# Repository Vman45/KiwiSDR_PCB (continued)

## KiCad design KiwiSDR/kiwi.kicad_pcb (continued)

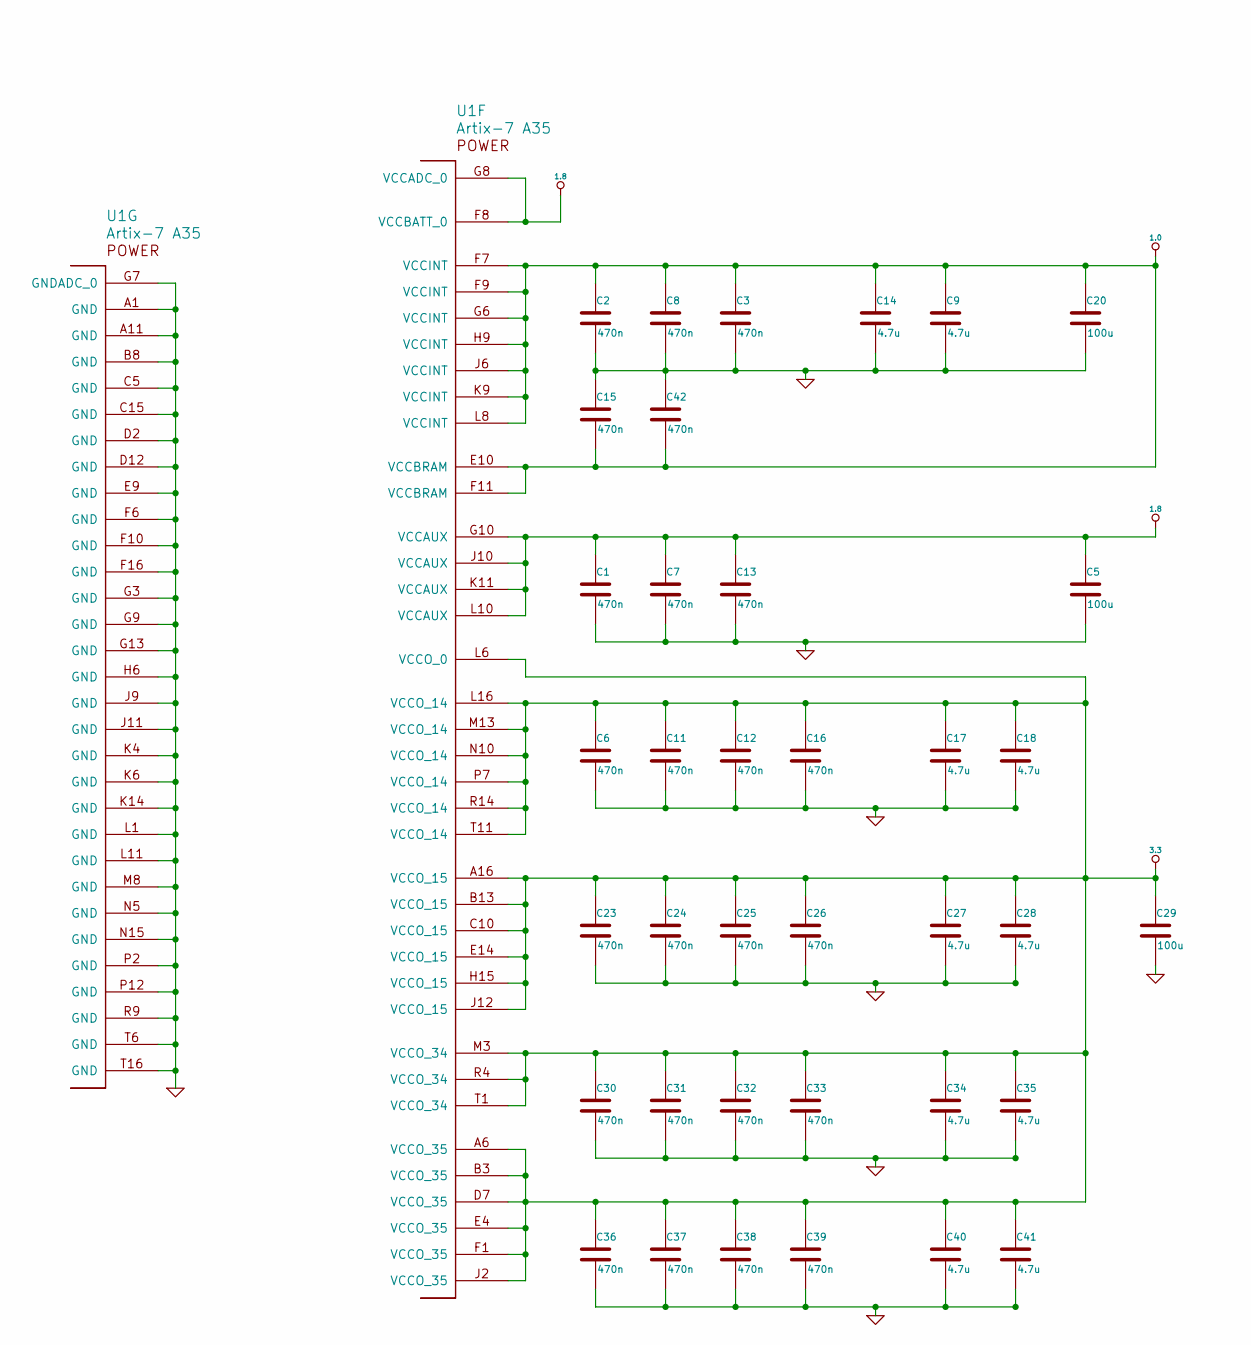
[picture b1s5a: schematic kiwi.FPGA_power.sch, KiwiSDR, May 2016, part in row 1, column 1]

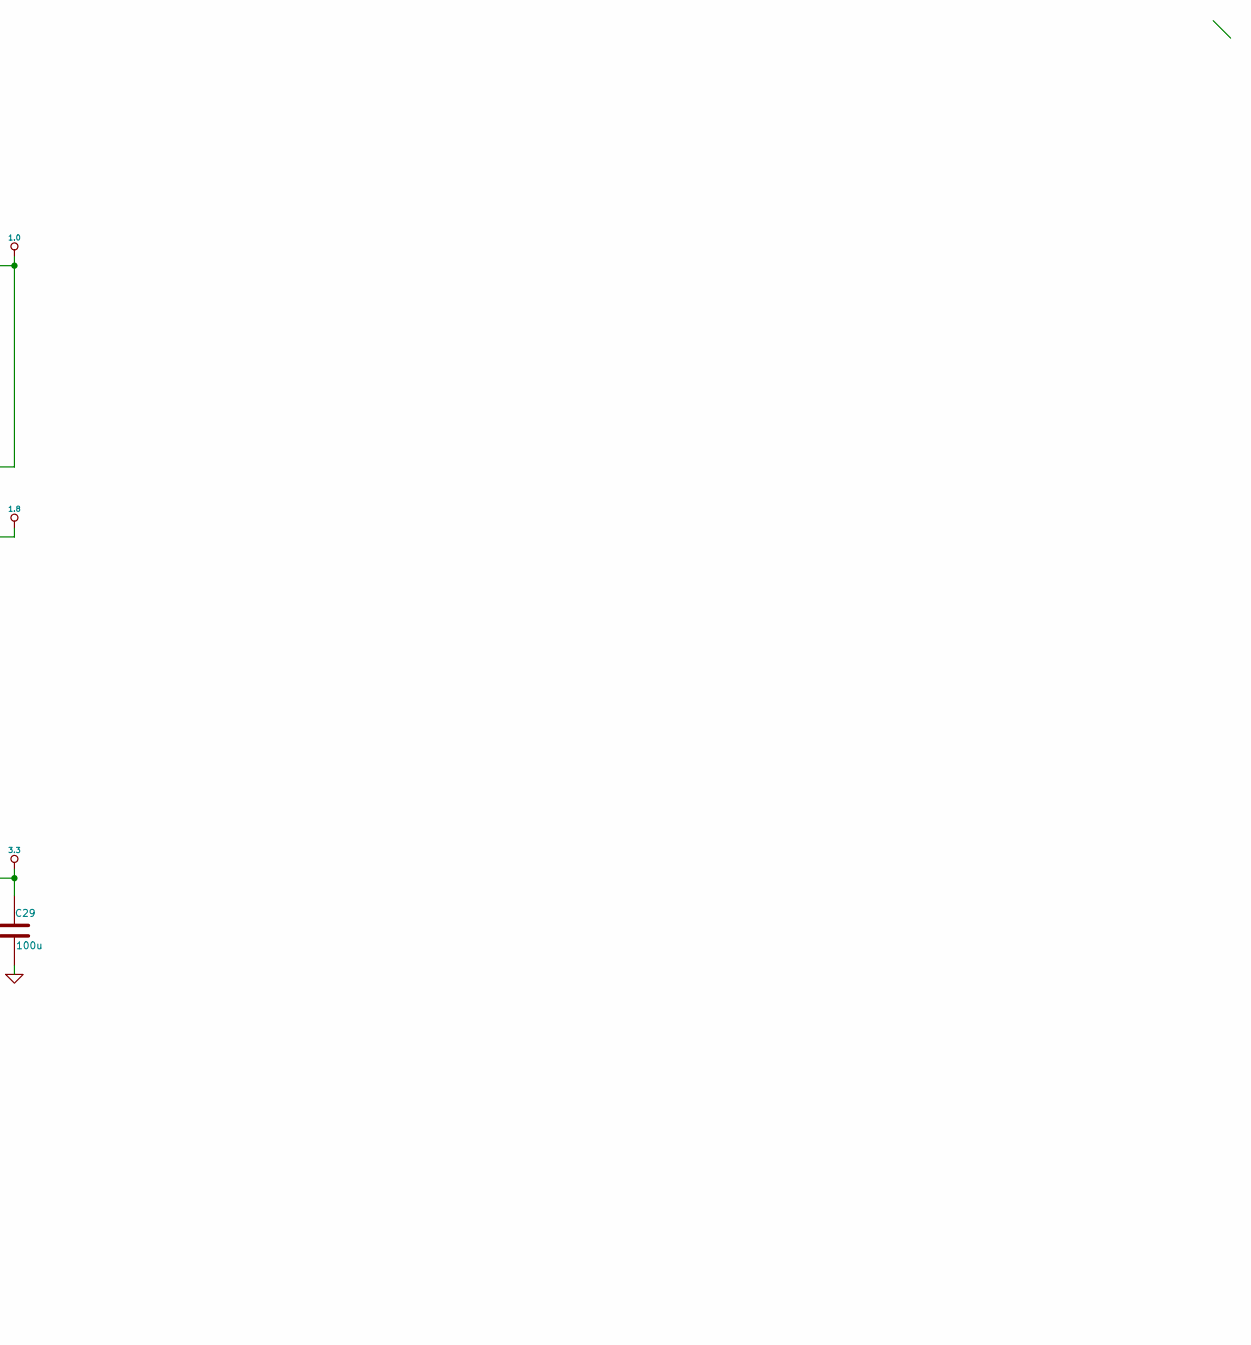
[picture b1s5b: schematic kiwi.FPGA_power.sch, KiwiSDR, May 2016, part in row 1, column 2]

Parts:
C1, C2, C3, C6, C7, C8, C11, C12, C13, C15, C16, C23, C24, C25, C26, C30, C31, C32, C33, C36, C37, C38, C39, C42: 470n; kiwi-SM0402
C5, C20, C29: 100u; kiwi-SM1206
C9, C14, C17, C18, C27, C28, C34, C35, C40, C41: 4.7u; kiwi-SM0402
U1: Artix-7 A35; kiwi-FTG256

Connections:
1.0: C2.1, C3.1, C8.1, C9.1, C14.1, C15.2, C20.1, C42.2, U1.E10 (VCCBRAM), U1.F7 (VCCINT), U1.F9 (VCCINT), U1.F11 (VCCBRAM), U1.G6 (VCCINT), U1.H9 (VCCINT), U1.J6 (VCCINT), U1.K9 (VCCINT), U1.L8 (VCCINT); also elsewhere on the board
1.8: C1.1, C5.1, C7.1, C13.1, U1.F8 (VCCBATT_0), U1.G8 (VCCADC_0), U1.G10 (VCCAUX), U1.J10 (VCCAUX), U1.K11 (VCCAUX), U1.L10 (VCCAUX); also elsewhere on the board

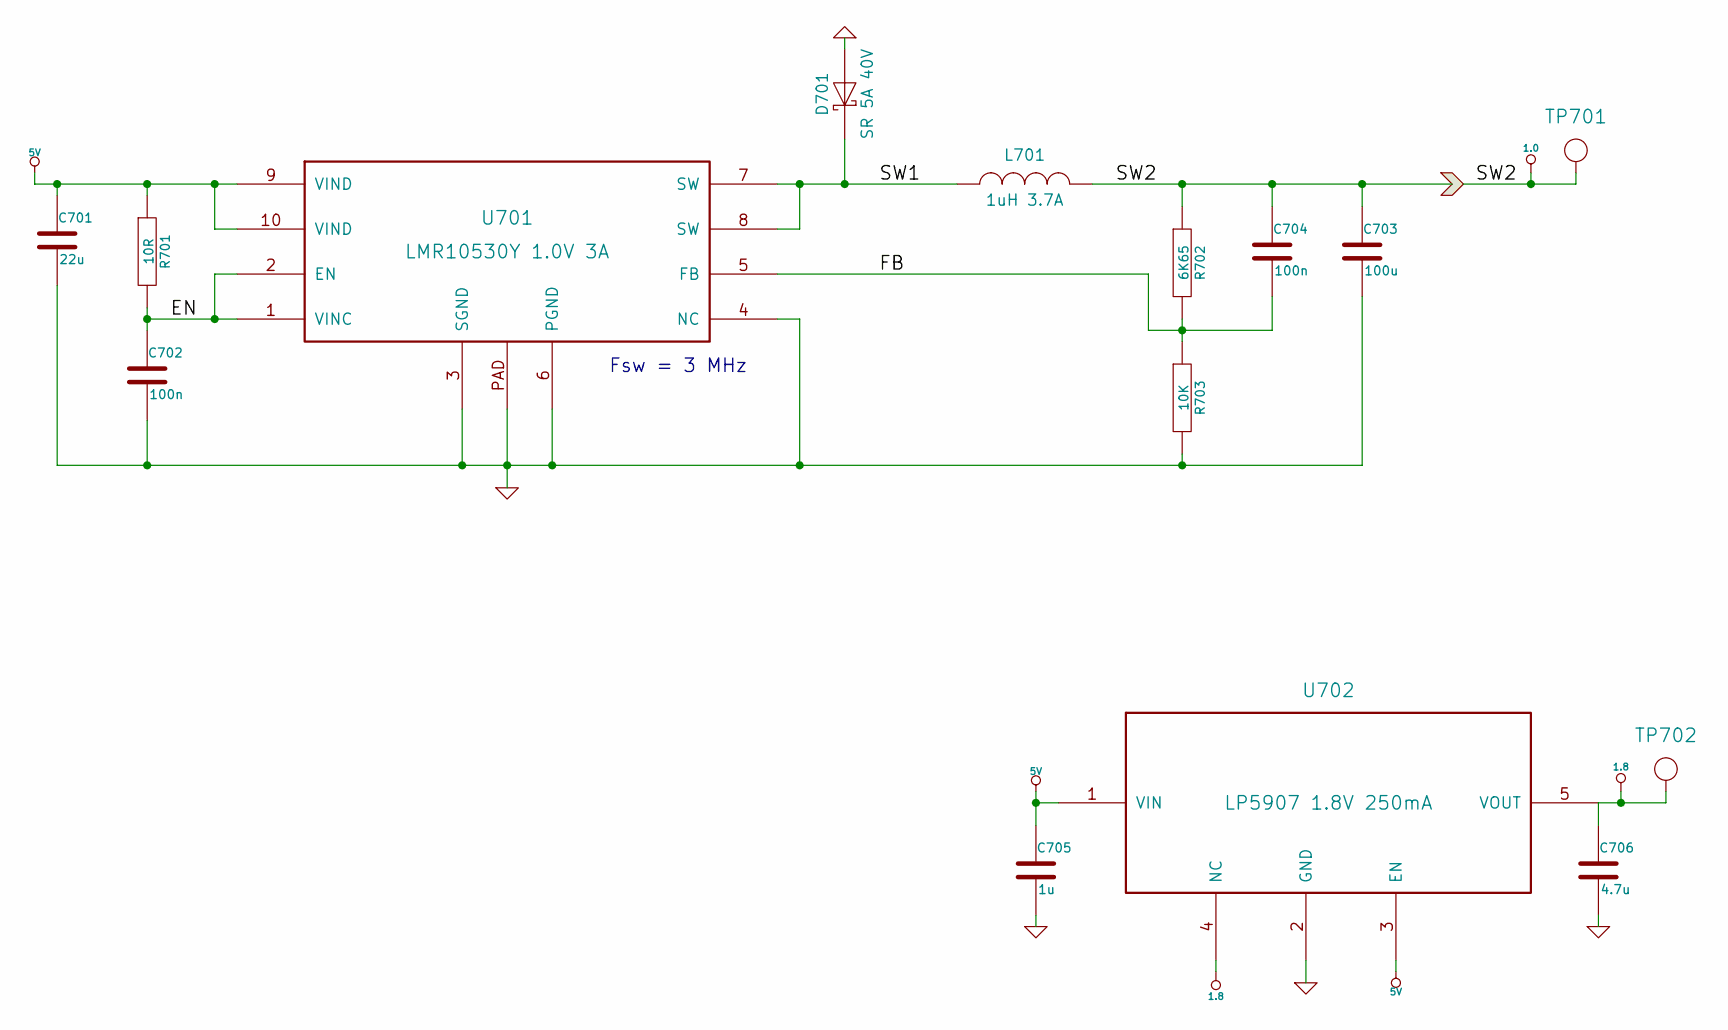
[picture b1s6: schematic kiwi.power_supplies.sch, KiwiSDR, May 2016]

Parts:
C701: 22u; kiwi-SM0805
C702, C704: 100n; kiwi-SM0402
C703: 100u; kiwi-SM1206
C705: 1u; kiwi-SM0402
C706: 4.7u; kiwi-SM0402
D701: SR 5A 40V; kiwi-DO214_AA
L701: 1uH 3.7A; kiwi-INDUCTOR_4x4
R701: 10R; kiwi-SM0402
R702: 6K65; kiwi-SM0402
R703: 10K; kiwi-SM0402
TP701, TP702: TEST_POINT; kiwi-TP_600
U701: LMR10530Y 1.0V 3A; kiwi-WSON10
U702: LP5907 1.8V 250mA; kiwi-SOT23_5

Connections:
1.0: C703.1, C704.1, L701.2, R702.1, TP701.1; also elsewhere on the board
1.8: C706.1, TP702.1, U702.4 (NC), U702.5 (VOUT); also elsewhere on the board
/Power_Supplies/EN: C702.1, R701.2, U701.1 (VINC), U701.2 (EN)
/Power_Supplies/FB: C704.2, R702.2, R703.1, U701.5 (FB)
/Power_Supplies/SW1: D701.1 (K), L701.1, U701.7 (SW), U701.8 (SW)

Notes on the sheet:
Fsw = 3 MHz

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
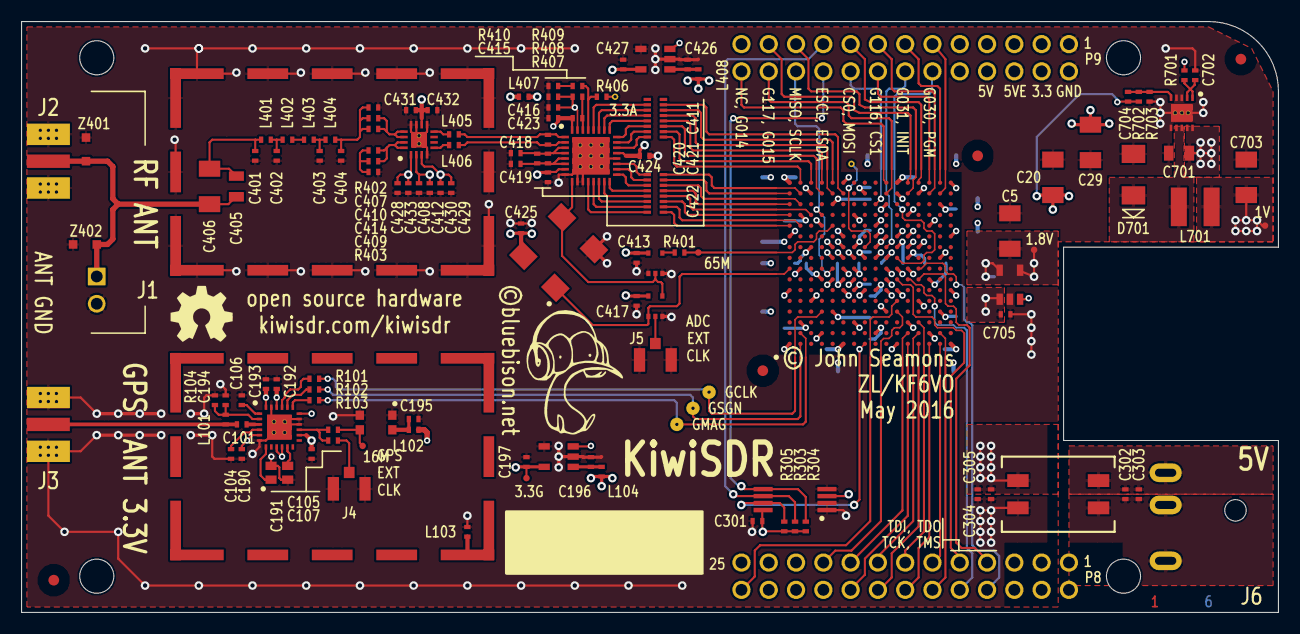
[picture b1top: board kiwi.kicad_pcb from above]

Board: 6 copper layers, 117.0 x 55.0 mm, 174 parts (0 on the bottom side), 119 nets.

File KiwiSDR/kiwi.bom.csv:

#1, 1, 0R, Panasonic, ERJ-2GE0R00X, kiwi-SM0402, R408
#2, 1, 10R, Panasonic, ERJ-2RKF10R0X, kiwi-SM0402, R701
#3, 1, 28R7, Panasonic, ERJ-2RKF28R7X, kiwi-SM0402, R403
#4, 1, 66R5, Panasonic, ERJ-2RKF66R5X, kiwi-SM0402, R402
#5, 4, 100R, Panasonic, ERJ-2RKF1000X, kiwi-SM0402, R101 R102 R103 R401
#6, 1, 1K5, Panasonic, ERJ-2RKF1501X, kiwi-SM0402, R104
#7, 3, 5K6, Panasonic, ERJ-2RKF5601X, kiwi-SM0402, R303 R304 R305
#8, 1, 6K65, Panasonic, ERJ-2RKF6651X, kiwi-SM0402, R702
#9, 4, 10K, Panasonic, ERJ-2RKF1002X, kiwi-SM0402, R406 R409 R410 R703
#10, 2, 100R, Bourns, CAY16-101J8LF, kiwi-RNET_CAY16_J8, R404 R405
#11, 2, 22p, Murata, GRM1555C1H220JA01D, kiwi-SM0402, C101 C104
#12, 2, 56p/100, Murata, GRM1555C2A560JA01D, kiwi-SM0402, C401 C404
#13, 4, 100p, Murata, GRM1555C1H101JA01D, kiwi-SM0402, C194 C408 C411 C416
#14, 2, 160p/50, Murata, GRM1555C1H161JA01D, kiwi-SM0402, C402 C403
#15, 5, 1n, Murata, GCM155R71H102KA37D, kiwi-SM0402, C407 C409 C428 C430 C432
#16, 8, 10n, Murata, GRM155R71C103KA01D, kiwi-SM0402, C105 C106 C193 C303 C305 C413 C417 C425
#17, 14, 100n, Murata, GRM155R71C104KA88D, kiwi-SM0402, C190 C191 C192 C195 C301 C421 C422 C423 C424 C429 C431 C433 C702 C704
#18, 28, 470n, Murata, GRM155R6YA474KE01D, kiwi-SM0402, C1 C2 C3 C6 C7 C8 C11 C12 C13 C15 C16 C23 C24 C25 C26 C30 C31 C32 C33 C36 C37 C38 C39 C42 C302 C304 C410 C414
#19, 7, 1u, Murata, GRM155R61E105KA12D, kiwi-SM0402, C196 C197 C418 C419 C426 C427 C705
#20, 3, 2.2u, Murata, GRM155R60J225ME15D, kiwi-SM0402, C412 C415 C420
#21, 11, 4.7u, Murata, GRM155R60J475ME47D, kiwi-SM0402, C9 C14 C17 C18 C27 C28 C34 C35 C40 C41 C706
#22, 1, 1n/100, Murata, GRM219R72A102KA01J, kiwi-SM0805, C405
#23, 1, 22u, Murata, GRM21BR60J226ME39L, kiwi-SM0805, C701
#24, 1, 470n/100, AVX, ESD61C474K4T2A-28, kiwi-SM1206, C406
#25, 4, 100u, Murata, GRM31CR60J107ME39L, kiwi-SM1206, C5 C20 C29 C703
#26, 5, FB 600Z, TDK, MMZ1005B601C, kiwi-SM0402, L102 L103 L104 L407 L408
#27, 1, 39nH, TDK, MLK1005S39NJ, kiwi-SM0402, L101
#28, 3, 150nH, TDK, MLG1005SR15J, kiwi-SM0402, L403 L405 L406
#29, 1, 270nH, TDK, MLG1005SR27J, kiwi-SM0402, L402
#30, 2, 330nH, TDK, MLG1005SR33J, kiwi-SM0402, L401 L404
#31, 1, 1uH 3.7A, Bourns, SRN4018-1R0Y, kiwi-INDUCTOR_4x4, L701
#32, 1, CMC 500uH 1A, Bourns, SRF0905A-501Y, kiwi-CMC, T301
#33, 1, SAW L1, RFM, SF1186G, kiwi-SAW, FL101
#34, 1, SE4150L, Skyworks, SE4150L-R, kiwi-QFN24, U101
#35, 1, EEPROM 32Kx8, On Semi, CAT24C256YI-GT3, kiwi-TSSOP8, U301
#36, 2, NC7SZ125, Fairchild, NC7SZ125P5X, kiwi-SC70_5, U403 U406
#37, 1, LMR10530Y 1.0V 3A, TI, LMR10530YSD/NOPB, kiwi-WSON10, U701
#38, 2, LP5907 3.3V 250mA, TI, LP5907QMFX-3.3Q1, kiwi-SOT23_5, U104 U404
#39, 1, LP5907 1.8V 250mA, TI, LP5907QMFX-1.8Q1, kiwi-SOT23_5, U702
#40, 1, SR 5A 40V, Vishay, SSB44-E3/52T, kiwi-DO214_AA, D701
#41, 2, TVS 3.3V, Bourns, CDSOD323-T03C, kiwi-SOD323, Z401 Z402
#42, 1, 66.6666 MHz, Conner Winfield, CWX823-066.6666M, kiwi-XO, U402
#43, 1, 16.368 MHz, TXC, 7Q-16.368MBG-T, kiwi-TCXO, X101
#44, 2, RF_SHIELD 29x19, Laird, BMI-S-209-F, *, ZR401 ZR101
#45, 2, RF_SHIELD_COVER 29x19, Laird, BMI-S-209-C, kiwi-RF_SHIELD_COVER, ZR102 ZR402
#46, 1, Artix-7 A35, Xilinx, XC7A35T-1FTG256C, kiwi-FTG256, U1
#47, 1, LTC2248, Linear Tech, LTC2248CUH#PBF, kiwi-QFN32, U401
#48, 1, LTC6401-20, Linear Tech, LTC6401CUD-20#PBF, kiwi-QFN16, U405

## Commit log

2016-10-07 long overdue update to v1.0 PCB files
    These are the files used in the current production PCBs.
2016-12-09 new silkscreen with more refs
2017-04-08 update to new Dropbox links
2017-11-01 fix page name
2018-05-27 updates to readme file
2018-05-27 add git diff target
